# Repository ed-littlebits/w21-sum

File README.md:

w21-sum
===============

Wire Bit that outputs a time-varying voltage equal to the sum of two time-varying input voltages between 0 and approximately 5 Volts.  Output is saturating (e.g. 3.5 V + 2.5 V = 5 V).

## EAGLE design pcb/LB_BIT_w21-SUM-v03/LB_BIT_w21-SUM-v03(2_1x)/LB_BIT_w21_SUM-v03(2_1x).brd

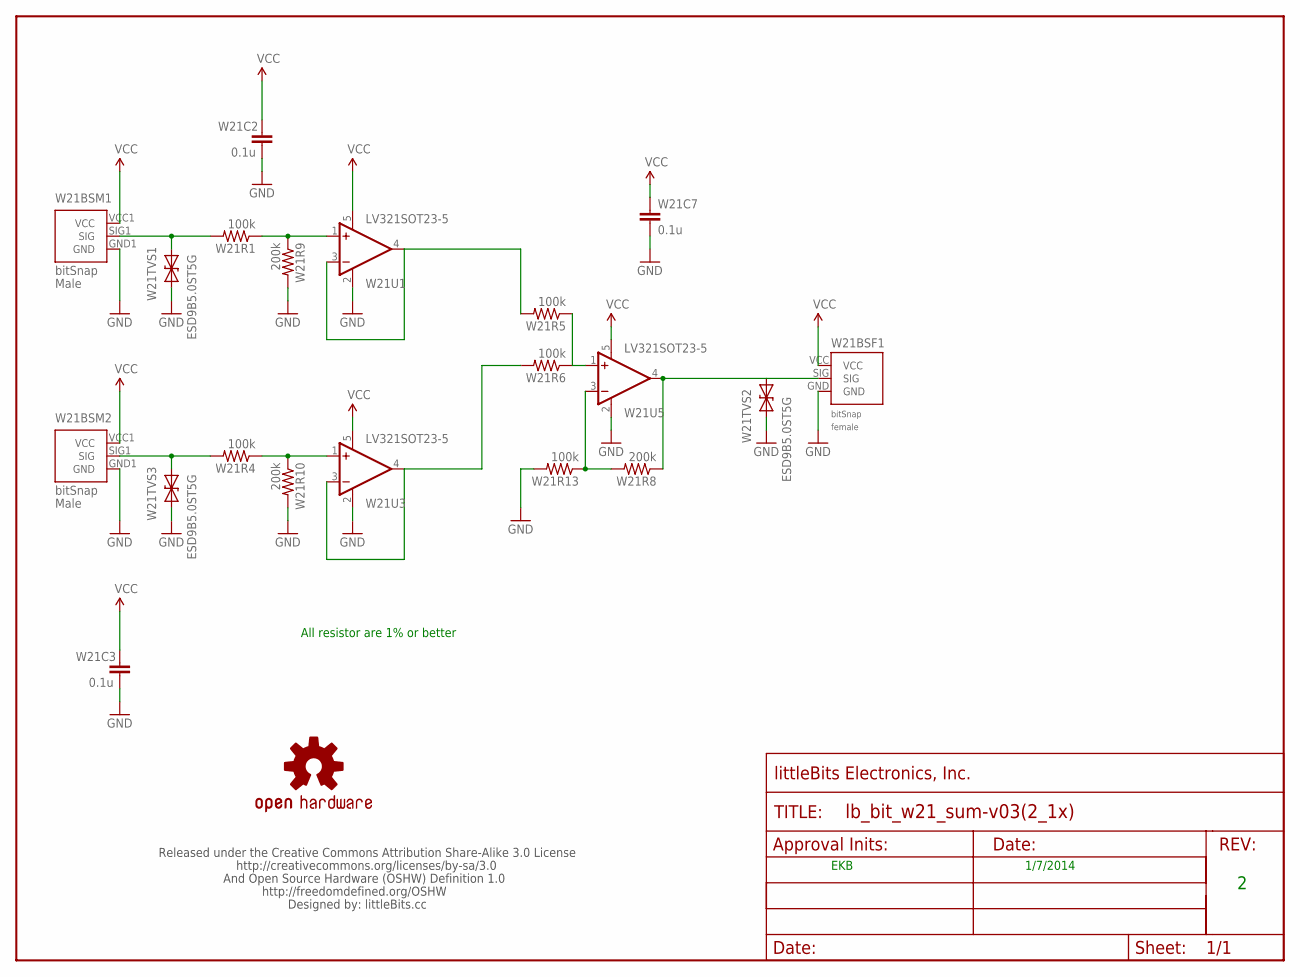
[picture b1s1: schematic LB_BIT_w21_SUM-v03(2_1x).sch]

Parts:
FRAME1: FRAME-LETTER; FABDWG01
U$1: OSHW-LOGOS; OSHW-LOGO-S
U$2: OSHWCREDIT
W21BSF1: BITSNAP_V03_FEMALE
W21BSM1, W21BSM2: BITSNAP_V03_MALE
W21C2, W21C3, W21C7: 0.1u; CAP-0603
W21R1, W21R4, W21R5, W21R6, W21R13: 100k; RES-0603
W21R8, W21R9, W21R10: 200k; RES-0603
W21TVS1, W21TVS2, W21TVS3: ESD9B5.0ST5G; SOD-923
W21U1, W21U3, W21U5: LV321SOT23-5; SOT23-5

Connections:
GND: W21BSF1.GND, W21BSM1.GND1 (GND), W21BSM2.GND1 (GND), W21C2.2, W21C3.2, W21C7.2, W21R9.2, W21R10.2, W21R13.2, W21TVS1.1 (A), W21TVS2.1 (A), W21TVS3.1 (A), W21U1.2 (V-), W21U3.2 (V-), W21U5.2 (V-)
unnamed: W21BSM2.SIG1 (SIG), W21R4.2, W21TVS3.2 (C)
unnamed: W21R1.1, W21R9.1, W21U1.1 (+IN)
unnamed: W21R5.1, W21R6.1, W21U5.1 (+IN)
unnamed: W21BSM1.SIG1 (SIG), W21R1.2, W21TVS1.2 (C)
unnamed: W21BSF1.SIG, W21R8.1, W21TVS2.2 (C), W21U5.4 (OUT)
unnamed: W21R5.2, W21U1.3 (-IN), W21U1.4 (OUT)
unnamed: W21R4.1, W21R10.1, W21U3.1 (+IN)
unnamed: W21R6.2, W21U3.3 (-IN), W21U3.4 (OUT)
unnamed: W21R8.2, W21R13.1, W21U5.3 (-IN)
VCC: W21BSF1.VCC, W21BSM1.VCC1 (VCC), W21BSM2.VCC1 (VCC), W21C2.1, W21C3.1, W21C7.1, W21U1.5 (V+), W21U3.5 (V+), W21U5.5 (V+)

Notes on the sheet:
All resistor are 1% or better
EKB
1/7/2014

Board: 2 copper layers, 23 parts (0 on the bottom side), 11 nets, no tracks yet.

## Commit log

2014-01-02 Update README.md
    Basic description
2014-01-02 Folder structure and initial schematic capture
2014-01-02 Upload Draft PRD, some datasheets, and initial schematic capture.
2014-01-02 Hiccup
2014-01-02 ReAdd draft PRD
2014-01-03 Tuned inputs and reference rail, though it may not be neccessary. Sketched out the DC mixer and output buffer.
2014-01-03 Update README.md
    Update README
2014-01-06 Actual circuit prototyped and revised.
2014-01-07 Second revision of schematic, and created simulation and PCB file
2014-01-08 Working on Layout
2014-01-08 Cleaned up errant files and fixed board outline

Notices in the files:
parts and their libraries:
LITTLEBITS: Released under the Creative Commons Attribution Share-Alike 3.0 License
LITTLEBITS: http://creativecommons.org/license/by-sa/3.0
LITTLEBITS: http://creativecommons.org/licenses/by-sa/3.0
